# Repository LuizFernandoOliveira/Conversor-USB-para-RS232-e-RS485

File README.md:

# Conversor USB para RS232 e RS485

## Descrição
Esta PCB trata-se de um circuito eletrônico que transforma uma única porta USB em múltiplos canais de comunicação serial industrial RS232 e/ou RS485.

---

## Descrições técnicas

- Interface USB: Dispositivo USB High-Speed de 480Mbps;
- Possui quatro canais RS232 (1 ao 4) e quatro canais RS485 (1 ao 4);
- Taxa de Transmissão (Baud Rate): Variável de 1200bps até 6Mbps;
- Alimentação Principal: Requer apenas 3.3V;
- Possui pinos de alimentação de saída de 3.3V e 5V;
- Buffering (FIFO):
  - RX FIFO: 2048 bytes por UART.
  - TX FIFO: 1024 bytes por UART.
- Configurações UART:
  - Bits de Dados: 8 bits;
  - Paridade: Ímpar, Par e Nenhuma;
  - Bits de Parada: 1 ou 2.

---

## Estrutura do repositório
Os arquivos de hardware foram desenvolvidos utilizando o KiCad 9.0.
- **`.kicad_pcb`**: Layout da placa de circuito impresso (Board).
- **`.kicad_sch`**: Esquemático eletrônico do sistema (Schematic).
- **`.kicad_pro`**: Gerenciador de projeto do KiCad (Project).

---

## Autor
**Dr. Luiz Fernando Pinto de Oliveira**

*Engenheiro Eletrônico especializado em Sistemas Embarcados e Ultra-Low Power.*
- **Website:** [FAPLO](https://faplo.webnode.page/)
- **LinkedIn:** [lfpo](https://www.linkedin.com/in/lfpo/)

---

Shield: [![CC BY-NC-ND 4.0][cc-by-nc-nd-shield]][cc-by-nc-nd]

This work is licensed under a
[Creative Commons Attribution-NonCommercial-NoDerivs 4.0 International License][cc-by-nc-nd].

[![CC BY-NC-ND 4.0][cc-by-nc-nd-image]][cc-by-nc-nd]

[cc-by-nc-nd]: http://creativecommons.org/licenses/by-nc-nd/4.0/
[cc-by-nc-nd-image]: https://licensebuttons.net/l/by-nc-nd/4.0/88x31.png
[cc-by-nc-nd-shield]: https://img.shields.io/badge/License-CC%20BY--NC--ND%204.0-lightgrey.svg

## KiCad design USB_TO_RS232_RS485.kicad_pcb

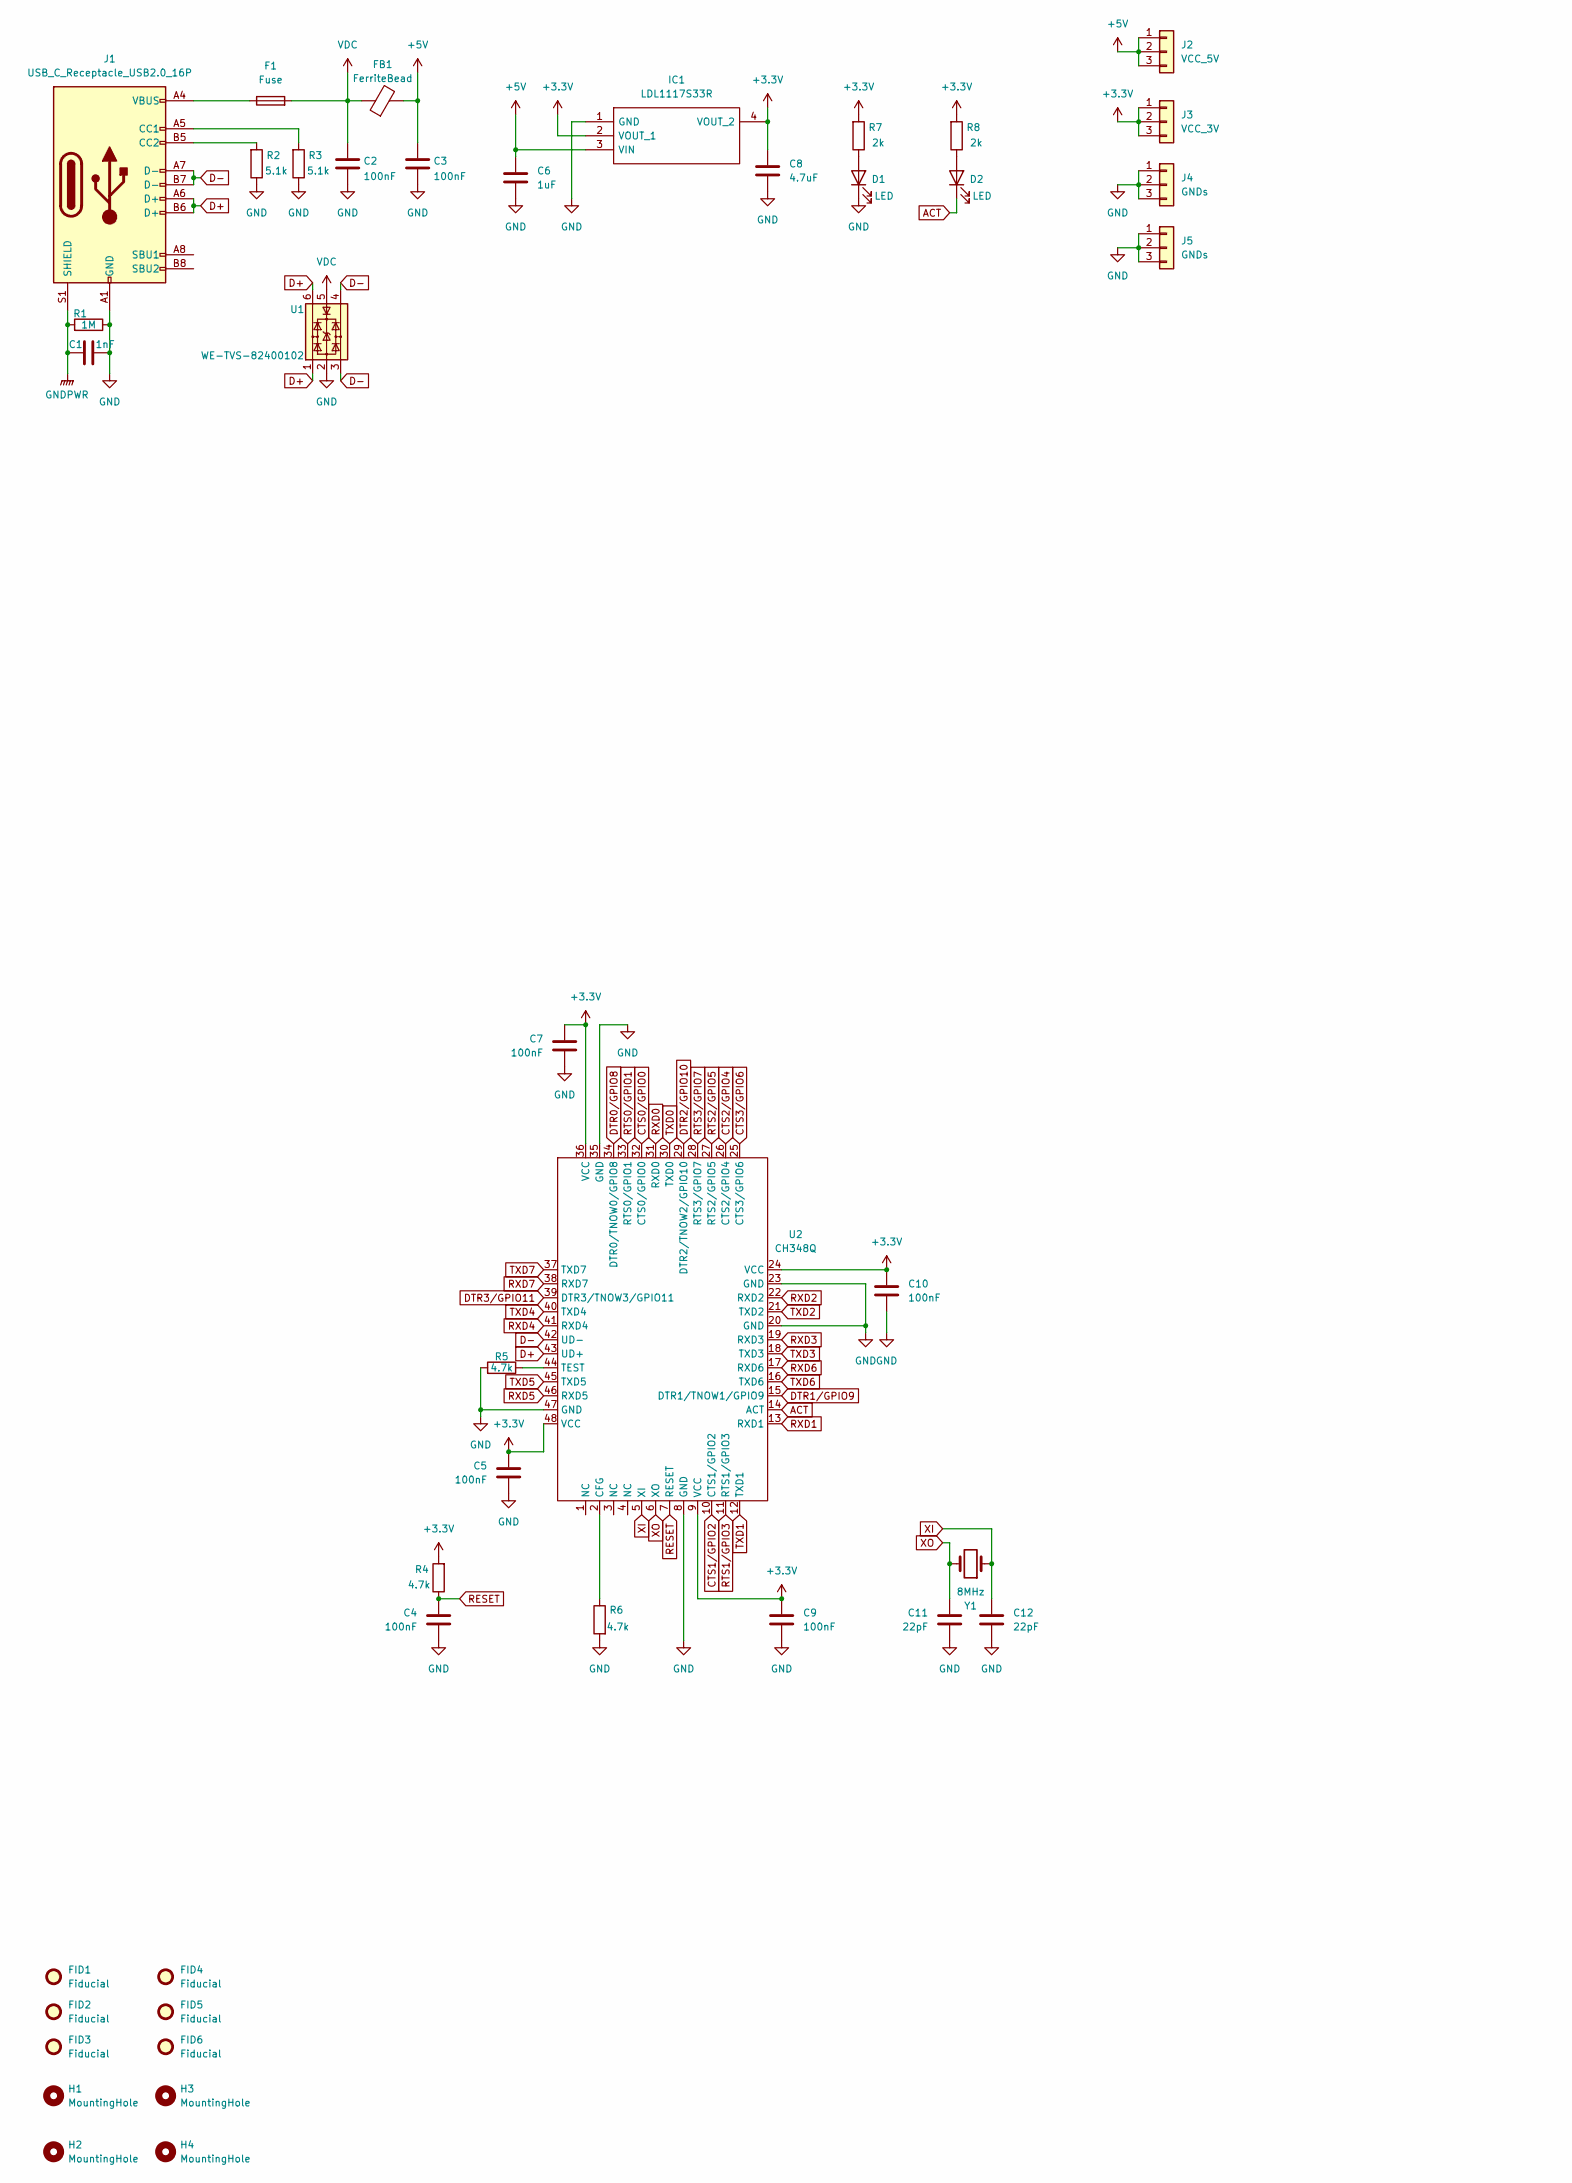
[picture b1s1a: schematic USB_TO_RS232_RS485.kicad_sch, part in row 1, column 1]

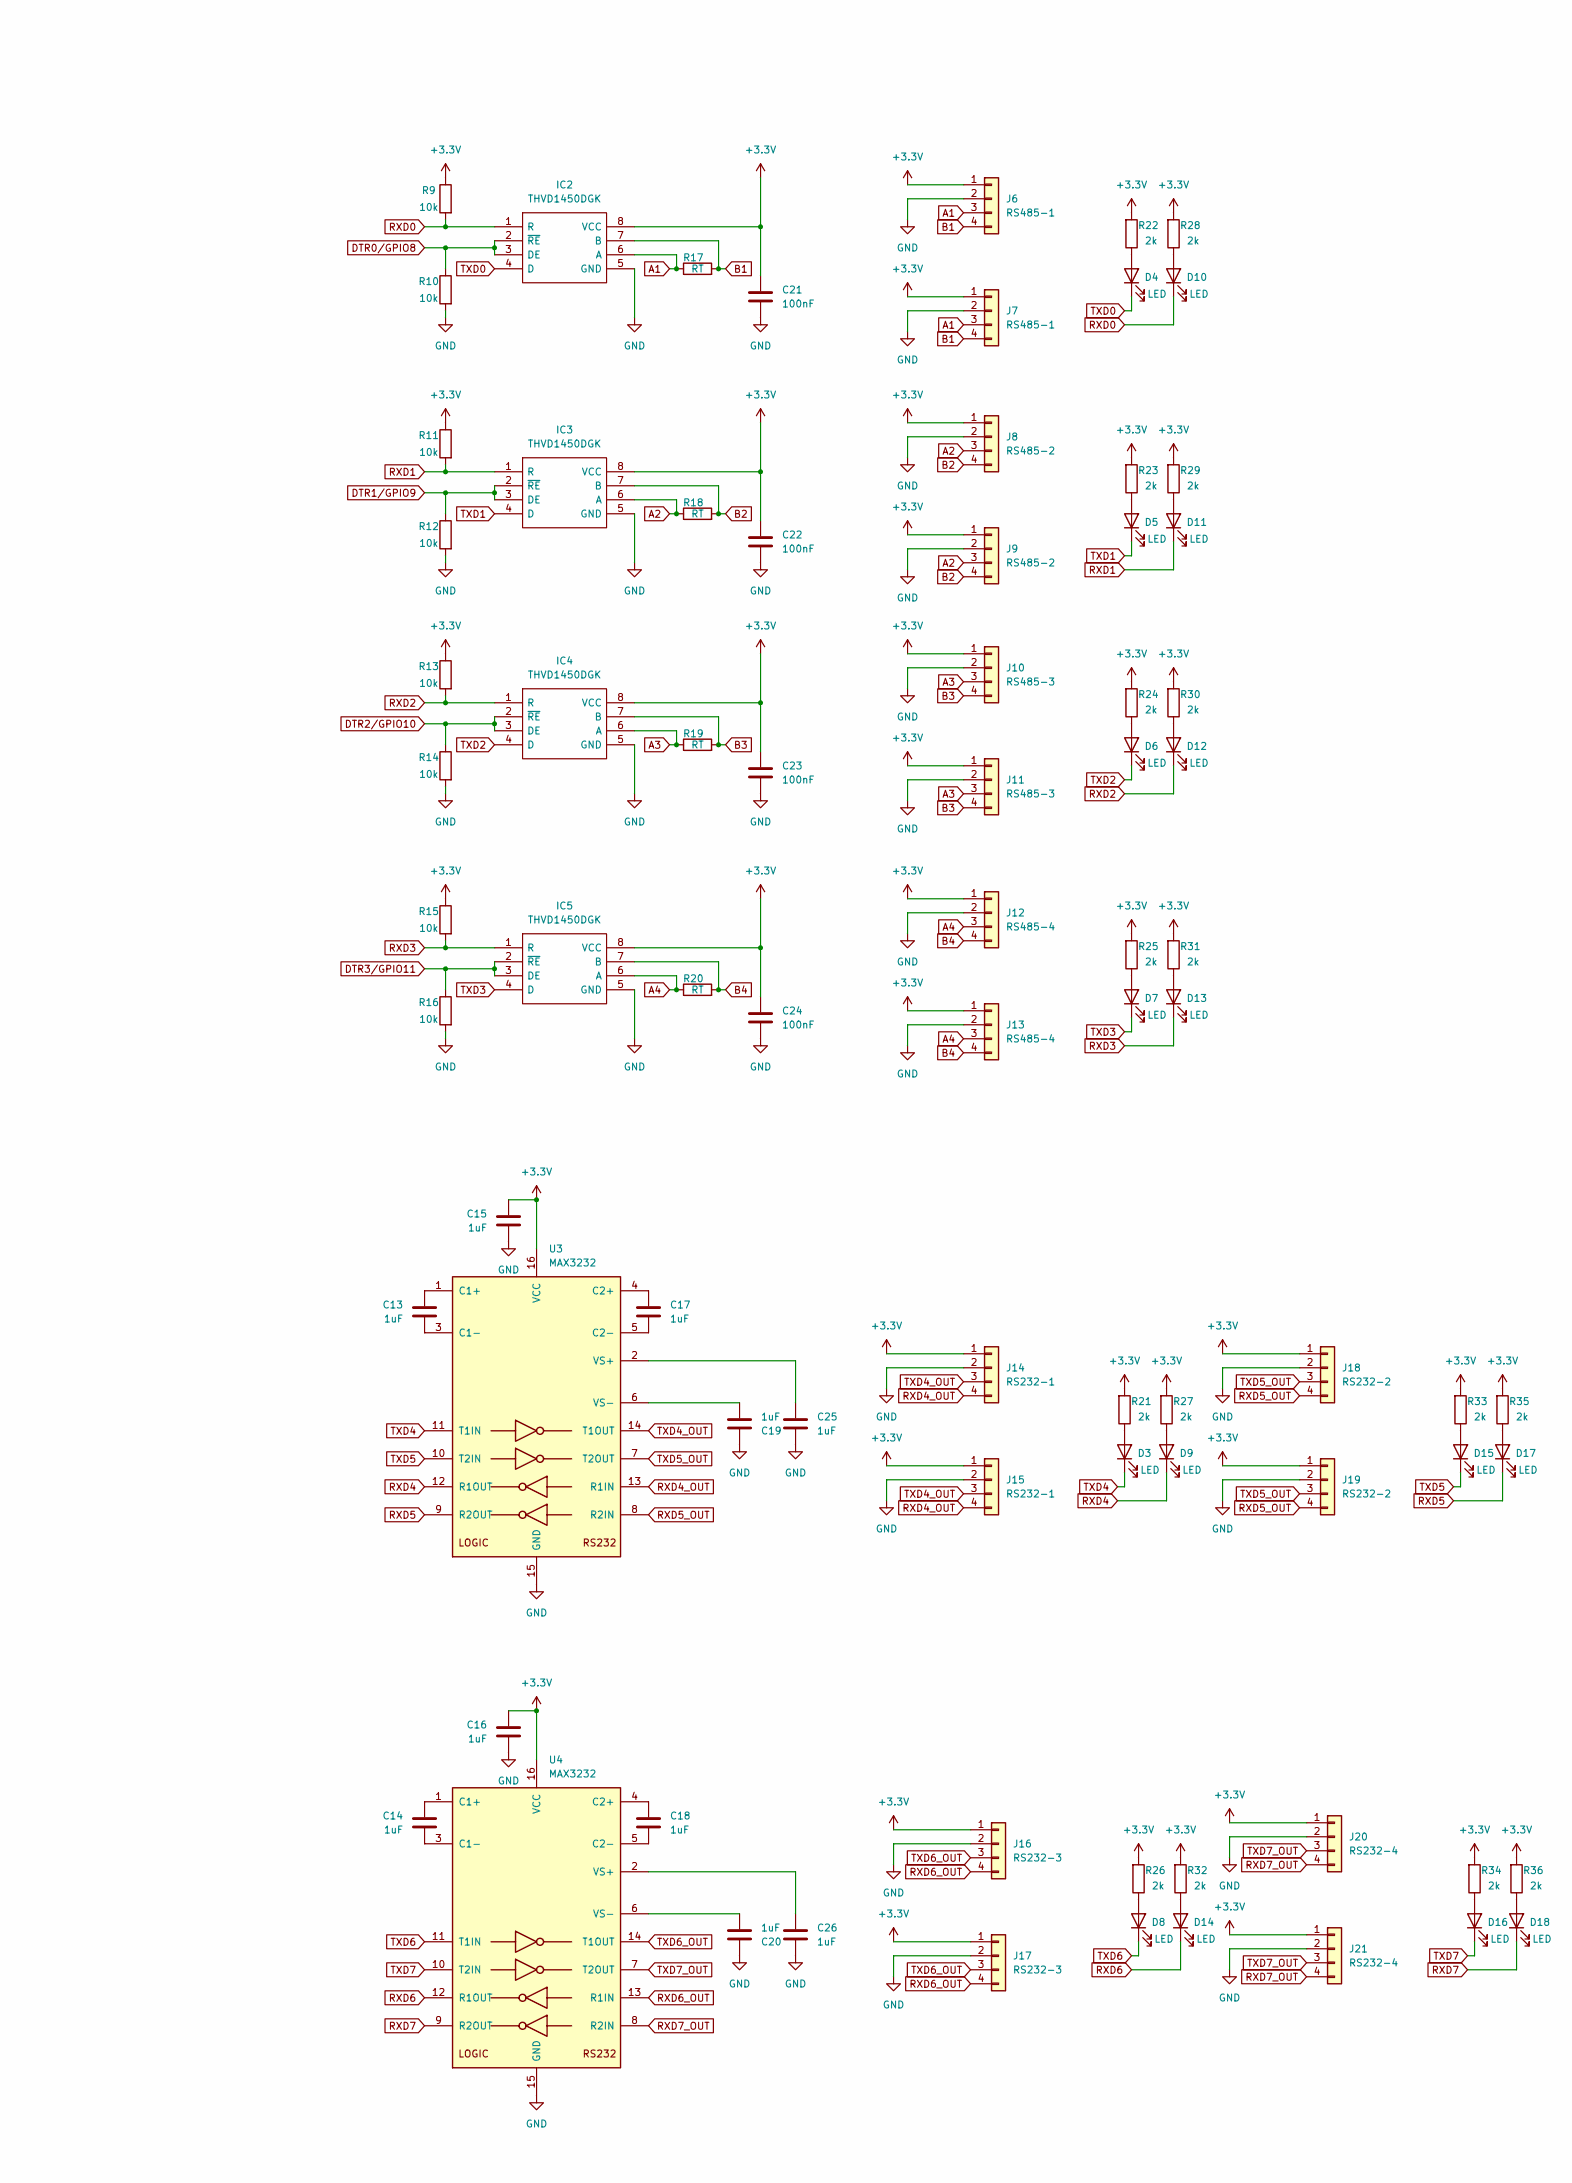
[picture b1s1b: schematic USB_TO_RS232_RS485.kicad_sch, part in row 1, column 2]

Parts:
C1: 1nF; C_0805_2012Metric
C2, C3, C4, C5, C7, C9, C10, C21, C22, C23, C24: 100nF; C_0805_2012Metric
C6, C13, C14, C15, C16, C17, C18, C19, C20, C25, C26: 1uF; C_0805_2012Metric
C8: 4.7uF; C_0805_2012Metric
C11, C12: 22pF; C_0805_2012Metric
D1, D2, D3, D4, D5, D6, D7, D8, D9, D10, D11, D12, D13, D14, D15, D16, D17, D18: LED; LED_0805_2012Metric
F1: Fuse; Fuse_0805_2012Metric
FB1: FerriteBead; L_0805_2012Metric
FID1, FID2, FID3, FID4, FID5, FID6: Fiducial; Fiducial_1mm_Mask2mm
H1, H2, H3, H4: MountingHole; MountingHole_3.2mm_M3_DIN965
IC1: LDL1117S33R; SOT230P700X180-4N; Manufacturer_Part_Number LDL1117S33R; Mouser Part Number 511-LDL1117S33R
IC2, IC3, IC4, IC5: THVD1450DGK; SOP65P490X110-8N; Manufacturer_Part_Number THVD1450DGK; Mouser Part Number 595-THVD1450DGK
J1: USB_C_Receptacle_USB2.0_16P; USB_C_Receptacle_HRO_TYPE-C-31-M-12
J2: VCC_5V; PinHeader_1x03_P2.54mm_Vertical
J3: VCC_3V; PinHeader_1x03_P2.54mm_Vertical
J4, J5: GNDs; PinHeader_1x03_P2.54mm_Vertical
J6: RS485-1; PinHeader_1x04_P2.54mm_Vertical
J7: RS485-1; PhoenixContact_MSTBA_2,5_4-G-5,08_1x04_P5.08mm_Horizontal
J8: RS485-2; PinHeader_1x04_P2.54mm_Vertical
J9: RS485-2; PhoenixContact_MSTBA_2,5_4-G-5,08_1x04_P5.08mm_Horizontal
J10: RS485-3; PinHeader_1x04_P2.54mm_Vertical
J11: RS485-3; PhoenixContact_MSTBA_2,5_4-G-5,08_1x04_P5.08mm_Horizontal
J12: RS485-4; PinHeader_1x04_P2.54mm_Vertical
J13: RS485-4; PhoenixContact_MSTBA_2,5_4-G-5,08_1x04_P5.08mm_Horizontal
J14: RS232-1; PinHeader_1x04_P2.54mm_Vertical
J15: RS232-1; PhoenixContact_MSTBA_2,5_4-G-5,08_1x04_P5.08mm_Horizontal
J16: RS232-3; PinHeader_1x04_P2.54mm_Vertical
J17: RS232-3; PhoenixContact_MSTBA_2,5_4-G-5,08_1x04_P5.08mm_Horizontal
J18: RS232-2; PinHeader_1x04_P2.54mm_Vertical
J19: RS232-2; PhoenixContact_MSTBA_2,5_4-G-5,08_1x04_P5.08mm_Horizontal
J20: RS232-4; PinHeader_1x04_P2.54mm_Vertical
J21: RS232-4; PhoenixContact_MSTBA_2,5_4-G-5,08_1x04_P5.08mm_Horizontal
R1: 1M; R_0805_2012Metric
R2, R3: 5.1k; R_0805_2012Metric
R4, R5, R6: 4.7k; R_0805_2012Metric
R7, R8, R21, R22, R23, R24, R25, R26, R27, R28, R29, R30, R31, R32, R33, R34, R35, R36: 2k; R_0805_2012Metric
R9, R10, R11, R12, R13, R14, R15, R16: 10k; R_0805_2012Metric
R17, R18, R19, R20: RT; R_1206_3216Metric
U1: WE-TVS-82400102; SOT-23-6
U2: CH348Q
U3, U4: MAX3232; TSSOP-16_4.4x5mm_P0.65mm
Y1: 8MHz; Crystal_SMD_3225-4Pin_3.2x2.5mm

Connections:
+3.3V: C5.1, C7.1, C8.1, C9.1, C10.1, C15.1, C16.1, C21.1, C22.1, C23.1, C24.1, IC1.2 (VOUT_1), IC1.4 (VOUT_2), IC2.8 (VCC), IC3.8 (VCC), IC4.8 (VCC), IC5.8 (VCC), J3.1, J3.2, J3.3, J6.1, J7.1, J8.1, J9.1, J10.1, J11.1, J12.1, J13.1, J14.1, J15.1, J16.1, J17.1, J18.1, J19.1, J20.1, J21.1, R4.2, R7.2, R8.2, R9.1, R11.1, R13.1, R15.1, R21.2, R22.2, R23.2, R24.2, R25.2, R26.2, R27.2, R28.2, R29.2, R30.2, R31.2, R32.2, R33.2, R34.2, R35.2, R36.2, U2.9 (VCC), U2.24 (VCC), U2.36 (VCC), U2.48 (VCC), U3.16 (VCC), U4.16 (VCC)
+5V: C3.1, C6.1, FB1.2, IC1.3 (VIN), J2.1, J2.2, J2.3
A1: IC2.6 (A), J6.3, J7.3, R17.1
A2: IC3.6 (A), J8.3, J9.3, R18.1
A3: IC4.6 (A), J10.3, J11.3, R19.1
A4: IC5.6 (A), J12.3, J13.3, R20.1
ACT: D2.1 (K), U2.14 (ACT)
B1: IC2.7 (B), J6.4, J7.4, R17.2
B2: IC3.7 (B), J8.4, J9.4, R18.2
B3: IC4.7 (B), J10.4, J11.4, R19.2
B4: IC5.7 (B), J12.4, J13.4, R20.2
CTS0/GPIO0: U2.32 (CTS0/GPIO0)
CTS1/GPIO2: U2.10 (CTS1/GPIO2)
CTS2/GPIO4: U2.26 (CTS2/GPIO4)
CTS3/GPIO6: U2.25 (CTS3/GPIO6)
D+: J1.A6 (D+), J1.B6 (D+), U1.1, U1.6, U2.43 (UD+)
D-: J1.A7 (D-), J1.B7 (D-), U1.3, U1.4, U2.42 (UD-)
DTR0/GPIO8: IC2.2 (~RE), IC2.3 (DE), R10.1, U2.34 (DTR0/TNOW0/GPIO8)
DTR1/GPIO9: IC3.2 (~RE), IC3.3 (DE), R12.1, U2.15 (DTR1/TNOW1/GPIO9)
DTR2/GPIO10: IC4.2 (~RE), IC4.3 (DE), R14.1, U2.29 (DTR2/TNOW2/GPIO10)
DTR3/GPIO11: IC5.2 (~RE), IC5.3 (DE), R16.1, U2.39 (DTR3/TNOW3/GPIO11)
GND: C1.2, C2.2, C3.2, C4.2, C5.2, C6.2, C7.2, C8.2, C9.2, C10.2, C11.2, C12.2, C15.2, C16.2, C19.1, C20.1, C21.2, C22.2, C23.2, C24.2, C25.2, C26.2, D1.1 (K), IC1.1 (GND), IC2.5 (GND), IC3.5 (GND), IC4.5 (GND), IC5.5 (GND), J1.A1 (GND), J1.A12 (GND), J1.B1 (GND), J1.B12 (GND), J4.1, J4.2, J4.3, J5.1, J5.2, J5.3, J6.2, J7.2, J8.2, J9.2, J10.2, J11.2, J12.2, J13.2, J14.2, J15.2, J16.2, J17.2, J18.2, J19.2, J20.2, J21.2, R1.1, R2.1, R3.1, R5.2, R6.2, R10.2, R12.2, R14.2, R16.2, U1.2, U2.8 (GND), U2.20 (GND), U2.23 (GND), U2.35 (GND), U2.47 (GND), U3.15 (GND), U4.15 (GND)
GNDPWR: C1.1, J1.S1 (SHIELD), R1.2
unnamed: D1.2 (A), R7.1
unnamed: D2.2 (A), R8.1
unnamed: D3.2 (A), R21.1
unnamed: D4.2 (A), R22.1
unnamed: D5.2 (A), R23.1
unnamed: D6.2 (A), R24.1
unnamed: D7.2 (A), R25.1
unnamed: D8.2 (A), R26.1
unnamed: D9.2 (A), R27.1
unnamed: D10.2 (A), R28.1
unnamed: D11.2 (A), R29.1
unnamed: D12.2 (A), R30.1
unnamed: D13.2 (A), R31.1
unnamed: D14.2 (A), R32.1
unnamed: D15.2 (A), R33.1
unnamed: D16.2 (A), R34.1
unnamed: D17.2 (A), R35.1
unnamed: D18.2 (A), R36.1
unnamed: F1.1, J1.A4 (VBUS), J1.A9 (VBUS), J1.B4 (VBUS), J1.B9 (VBUS)
unnamed: J1.A5 (CC1), R3.2
unnamed: J1.B5 (CC2), R2.2
unnamed: R6.1, U2.2 (CFG)
unnamed: R5.1, U2.44 (TEST)
unnamed: C13.1, U3.1 (C1+)
unnamed: C13.2, U3.3 (C1-)
unnamed: C17.1, U3.4 (C2+)
unnamed: C17.2, U3.5 (C2-)
unnamed: C25.1, U3.2 (VS+)
unnamed: C19.2, U3.6 (VS-)
unnamed: C14.1, U4.1 (C1+)
unnamed: C14.2, U4.3 (C1-)
unnamed: C18.1, U4.4 (C2+)
unnamed: C18.2, U4.5 (C2-)
unnamed: C26.1, U4.2 (VS+)
unnamed: C20.2, U4.6 (VS-)
RESET: C4.1, R4.1, U2.7 (RESET)
RTS0/GPIO1: U2.33 (RTS0/GPIO1)
RTS1/GPIO3: U2.11 (RTS1/GPIO3)
RTS2/GPIO5: U2.27 (RTS2/GPIO5)
RTS3/GPIO7: U2.28 (RTS3/GPIO7)
RXD0: D10.1 (K), IC2.1 (R), R9.2, U2.31 (RXD0)
RXD1: D11.1 (K), IC3.1 (R), R11.2, U2.13 (RXD1)
RXD2: D12.1 (K), IC4.1 (R), R13.2, U2.22 (RXD2)
RXD3: D13.1 (K), IC5.1 (R), R15.2, U2.19 (RXD3)
RXD4: D9.1 (K), U2.41 (RXD4), U3.12 (R1OUT)
RXD4_OUT: J14.4, J15.4, U3.13 (R1IN)
RXD5: D17.1 (K), U2.46 (RXD5), U3.9 (R2OUT)
RXD5_OUT: J18.4, J19.4, U3.8 (R2IN)
RXD6: D14.1 (K), U2.17 (RXD6), U4.12 (R1OUT)
RXD6_OUT: J16.4, J17.4, U4.13 (R1IN)
RXD7: D18.1 (K), U2.38 (RXD7), U4.9 (R2OUT)
RXD7_OUT: J20.4, J21.4, U4.8 (R2IN)
TXD0: D4.1 (K), IC2.4 (D), U2.30 (TXD0)
TXD1: D5.1 (K), IC3.4 (D), U2.12 (TXD1)
TXD2: D6.1 (K), IC4.4 (D), U2.21 (TXD2)
TXD3: D7.1 (K), IC5.4 (D), U2.18 (TXD3)
TXD4: D3.1 (K), U2.40 (TXD4), U3.11 (T1IN)
TXD4_OUT: J14.3, J15.3, U3.14 (T1OUT)
TXD5: D15.1 (K), U2.45 (TXD5), U3.10 (T2IN)
TXD5_OUT: J18.3, J19.3, U3.7 (T2OUT)
TXD6: D8.1 (K), U2.16 (TXD6), U4.11 (T1IN)
TXD6_OUT: J16.3, J17.3, U4.14 (T1OUT)
TXD7: D16.1 (K), U2.37 (TXD7), U4.10 (T2IN)
TXD7_OUT: J20.3, J21.3, U4.7 (T2OUT)
VDC: C2.1, F1.2, FB1.1, U1.5
XI: C12.1, U2.5 (XI), Y1.1
XO: C11.1, U2.6 (XO), Y1.2

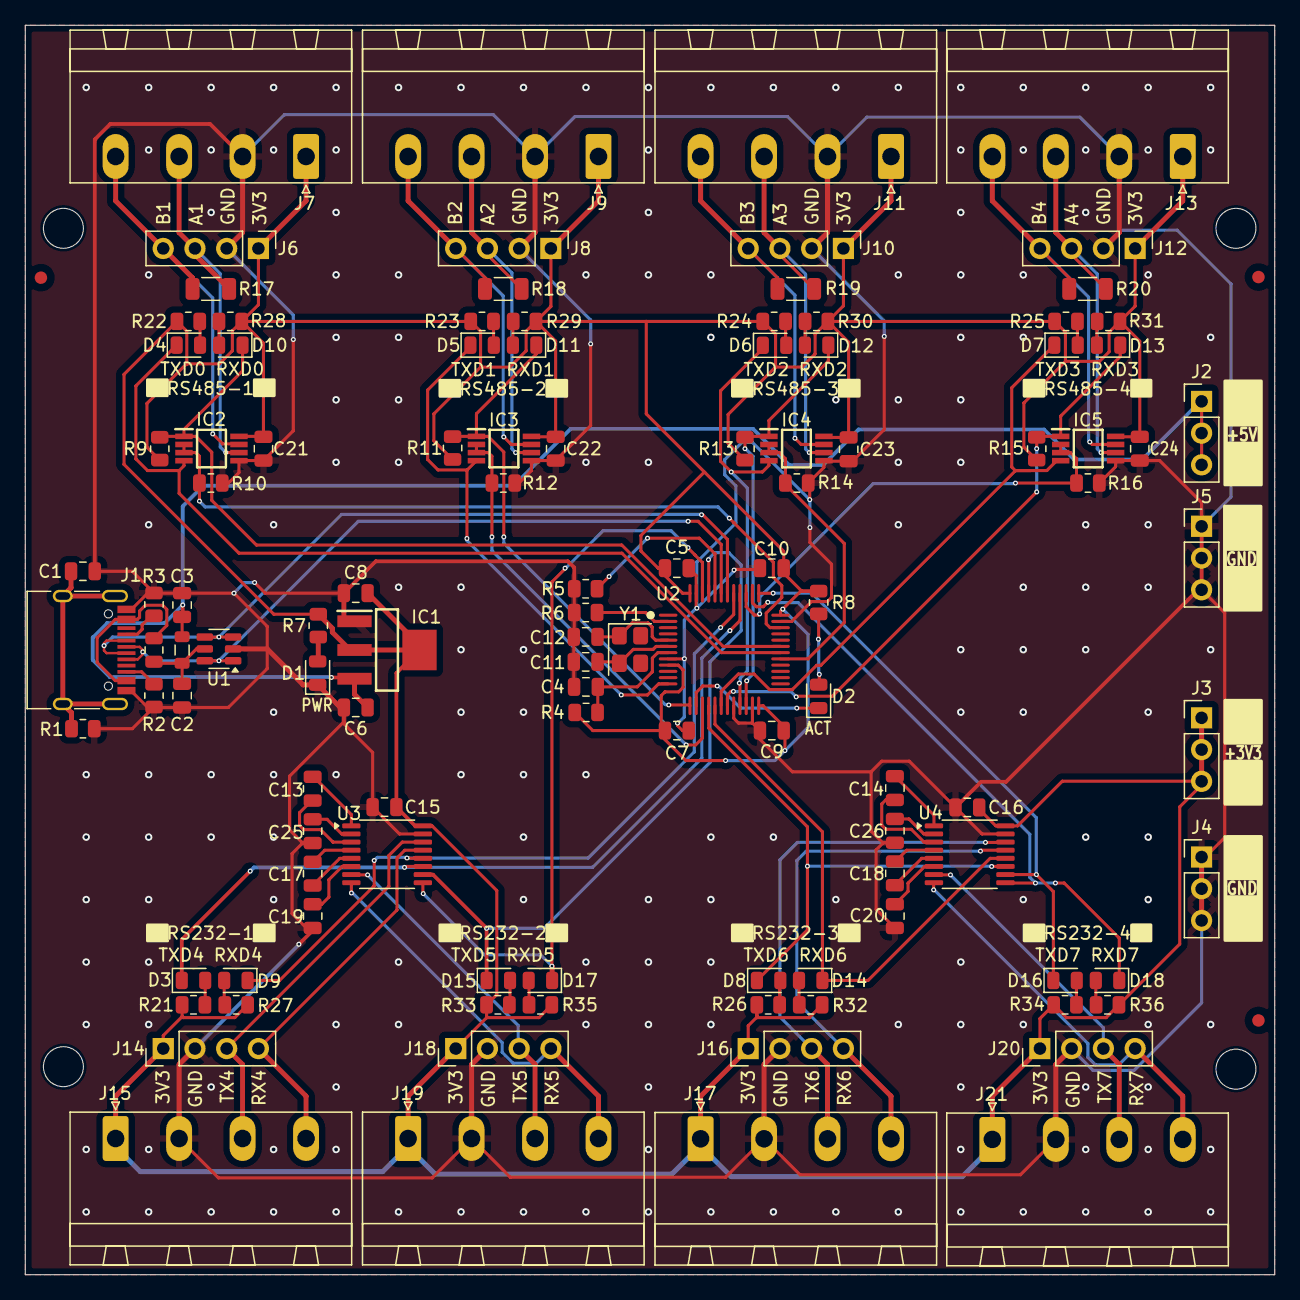
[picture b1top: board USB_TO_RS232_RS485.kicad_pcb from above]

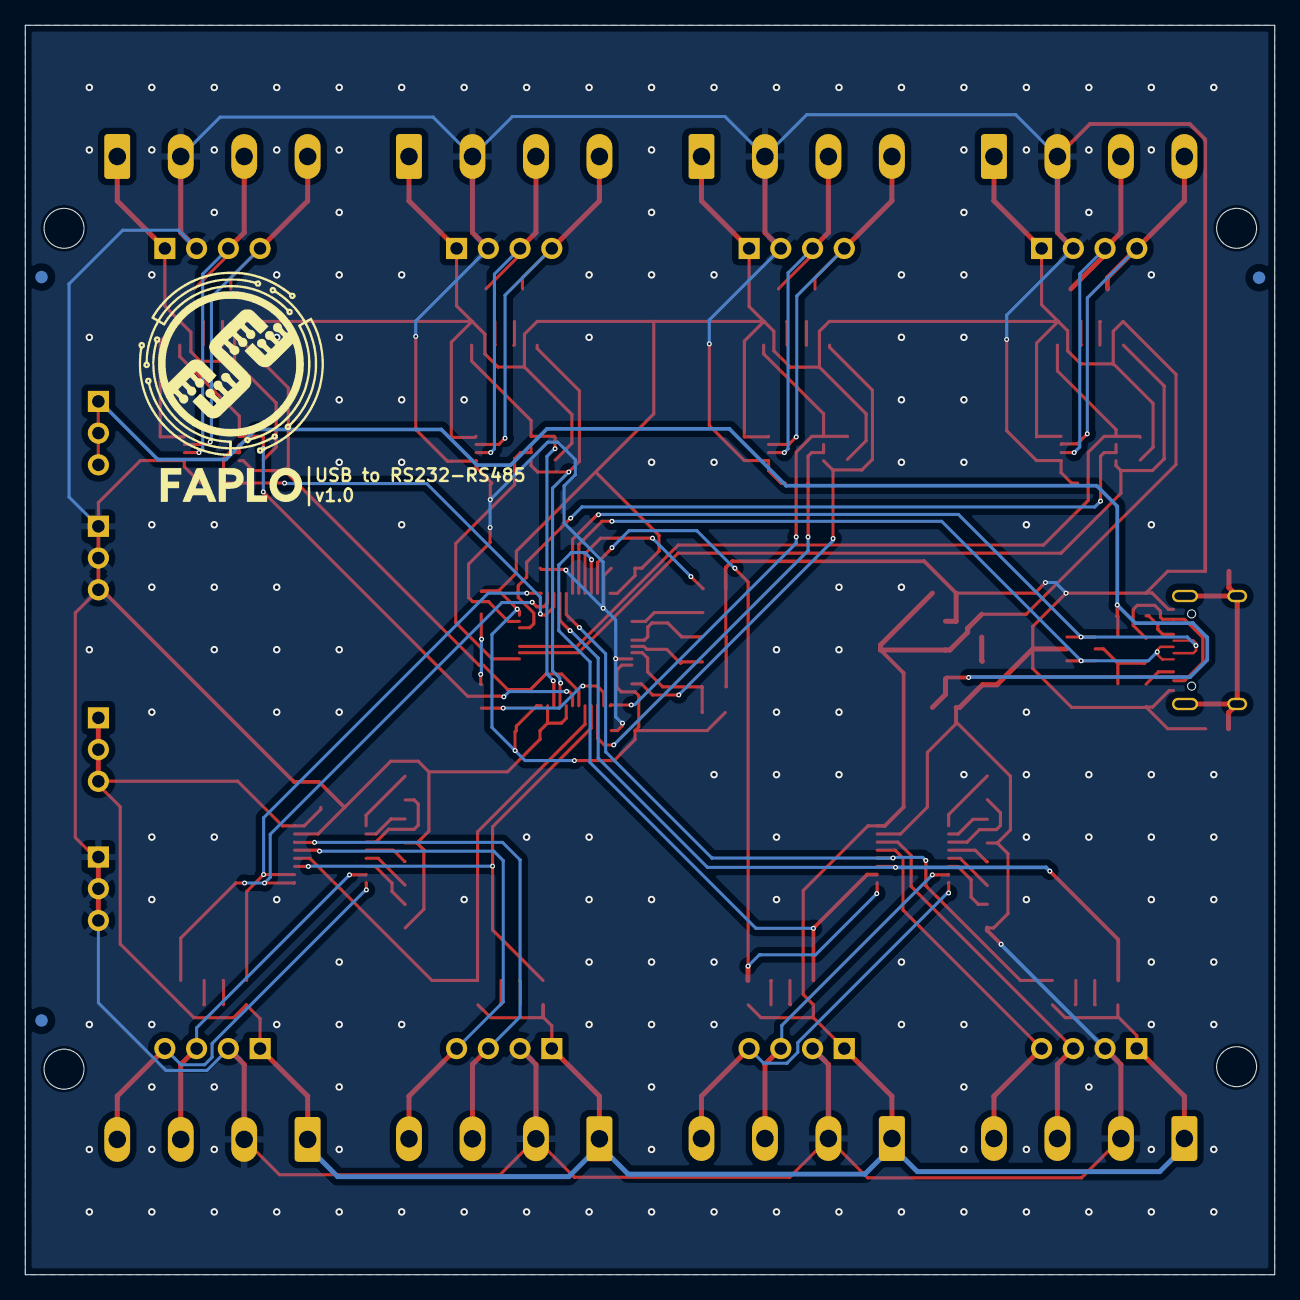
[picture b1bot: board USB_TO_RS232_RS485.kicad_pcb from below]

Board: 2 copper layers, 100.0 x 100.0 mm, 123 parts (3 on the bottom side), 82 nets.

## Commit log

2026-04-17 Inicialização de repositório
2026-04-17 Enhance README with project status and technical details
    Added project status and detailed technical descriptions.
2026-04-17 Add LICENSE file with CC BY-NC-ND 4.0 license
    Added Creative Commons Attribution-NonCommercial-NoDerivatives 4.0 International Public License to the project.
